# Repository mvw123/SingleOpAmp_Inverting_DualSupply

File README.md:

SingleOpAmp_Inverting_DualSupply 
================================

[WIP - NOT TESTED]
Ki CAD open source files
PCB was produced at OSHPark
requires a positive and a negative power supply. To do this connect the ground (-) to the positive (+) of another battery.
It is easiest to do this with 2 x 9v batteries.

there are a large number of library files here, most of which just need deleting.

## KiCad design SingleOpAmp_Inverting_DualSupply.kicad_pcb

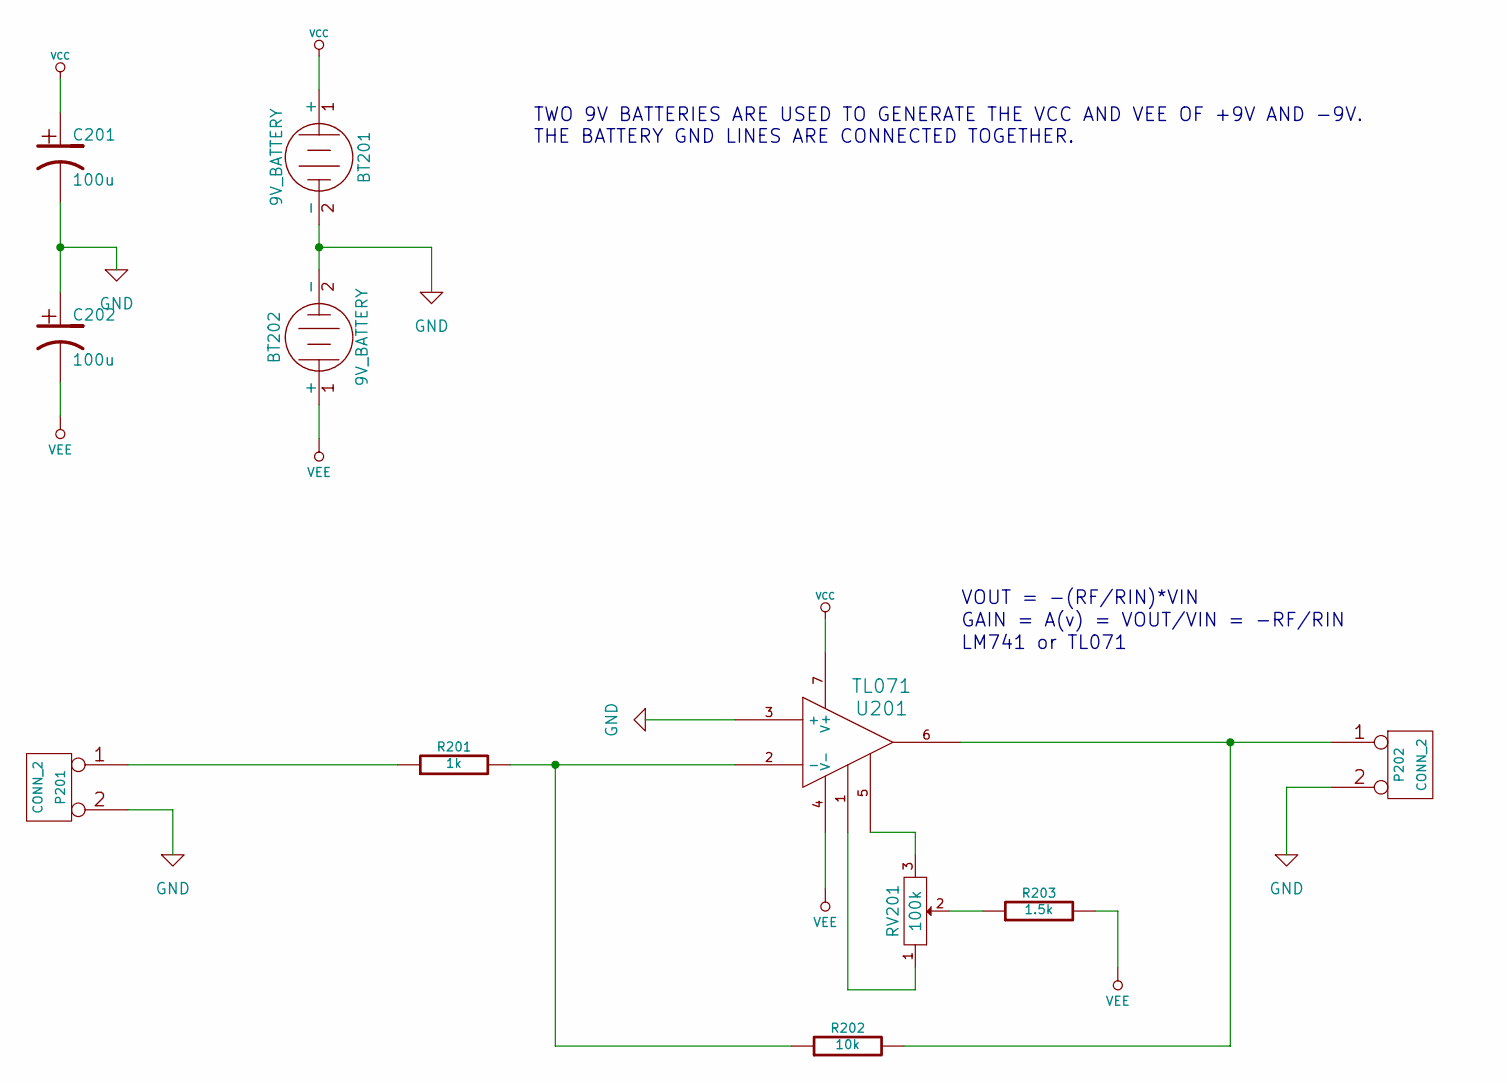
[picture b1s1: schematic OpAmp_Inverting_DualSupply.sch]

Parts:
BT201, BT202: 9V_BATTERY
C201, C202: 100u
P201, P202: CONN_2
R201: 1k
R202: 10k
R203: 1.5k
RV201: 100k
U201: TL071

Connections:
GND: BT201.2 (-), BT202.2 (-), C201.2, C202.1, P201.2 (PM), P202.2 (PM), U201.3 (+)
unnamed: RV201.1, U201.1
unnamed: R201.2, R202.1, U201.2 (-)
unnamed: R203.1, RV201.2
unnamed: P202.1, R202.2, U201.6
unnamed: RV201.3, U201.5
unnamed: P201.1, R201.1
VCC: BT201.1 (+), C201.1, U201.7 (V+)
VEE: BT202.1 (+), C202.2, R203.2, U201.4 (V-)

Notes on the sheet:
TWO 9V BATTERIES ARE USED TO GENERATE THE VCC AND VEE OF +9V AND -9V. THE BATTERY GND LINES ARE CONNECTED TOGETHER.
LM741 or TL071
VOUT = -(RF/RIN)*VIN
GAIN = A(v) = VOUT/VIN = -RF/RIN

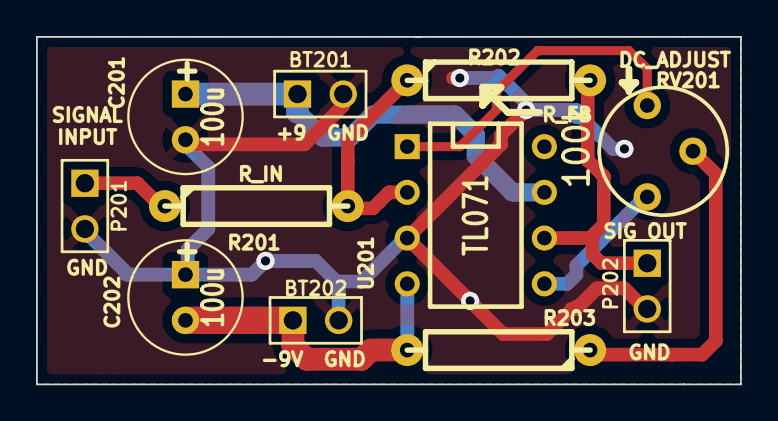
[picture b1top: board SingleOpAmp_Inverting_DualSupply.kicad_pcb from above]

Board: 2 copper layers, 39.1 x 19.3 mm, 11 parts (0 on the bottom side), 9 nets.

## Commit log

2014-05-02 Initial commit
    Initial commit
2014-05-02 added WIP comment
2014-05-02 added test notes
2016-01-15 unknown updates
    unknown updates
